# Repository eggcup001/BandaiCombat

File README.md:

# ATtiny85 Combat LED Game

ATtiny85 を使ってバンダイ「コンバット」風のLSIゲームを再現するための C プロジェクトです。

## Hardware

- MCU: ATtiny85, internal 8MHz, 3V
- LED matrix: 5 x 4
- 74HC595 x 2: LED anode bus and row/digit selection
- Buttons: 5-button ADC ladder
- Display: two common-cathode 7-segment digits
- Sound: 9042_16R electromagnetic passive buzzer

## Pin assignment

| Pin | Role |
|---|---|
| PB0 | 74HC595 SER |
| PB1 | 74HC595 SRCLK |
| PB2 | 74HC595 RCLK / LATCH |
| PB3 | ADC button ladder |
| PB4 | Buzzer driver |

## Display

U4 is the tens digit and U5 is the ones digit.

```text
U4 U5
 0  0   counter 00
    3   score 3
```

- Wait screen: score
- Game start: counter starts at `00`
- Normal play: zero-padded up-counter
- Enemy defeated: score for about 500 ms, then the next stage waits for FIRE
- Game over: the final score remains visible
- FIRE starts or restarts the game directly

## Game notes

- Mines are invisible.
- Mine proximity in the four orthogonally adjacent cells is indicated by sound only.
- Diagonal mines are not detected and do not produce the warning sound.
- The mine warning uses a low 1100 Hz pulse, distinct from the normal 2500 Hz tick.
- The death effect is a low descending tone from 1500 Hz to 500 Hz.
- Player is bright.
- Enemy uses one-eighth brightness and blinks on wait screens.
- Enemy dimming is scan-synchronized at about 83 Hz to avoid visible flicker.
- Mine placement always preserves a safe path to an orthogonally adjacent
  attack position next to the enemy.
- Stage randomization mixes PB3 ADC noise with the timing of FIRE input.
- Startup samples the PB3 ADC repeatedly before generating the first stage.
- The first stage shown during the wait screen is kept unchanged when FIRE
  starts play.
- Death restarts the same stage layout.
- Press FIRE to enter attack mode, then press a direction key to attack the
  adjacent cell in that direction.
- The direction key is consumed by the attack and does not move the player.
- A missed attack returns to movement mode without moving the player.
- A successful attack prepares the next round and waits for FIRE before play resumes.
- Press FIRE again while in attack mode to cancel it and return to movement
  mode.

## Build

```bash
make
```

## Flash

```bash
make flash
```

## Fuse example

```bash
make fuse
```

Fuse values:

- LFUSE: `0xE2`
- HFUSE: `0xDF`
- EFUSE: `0xFF`

These are intended for internal 8MHz, CKDIV8 disabled, reset enabled, BOD disabled.

## Important hardware tuning

`src/layer2/buttons.c` contains ADC thresholds.  
These must be adjusted using real measured ADC values.

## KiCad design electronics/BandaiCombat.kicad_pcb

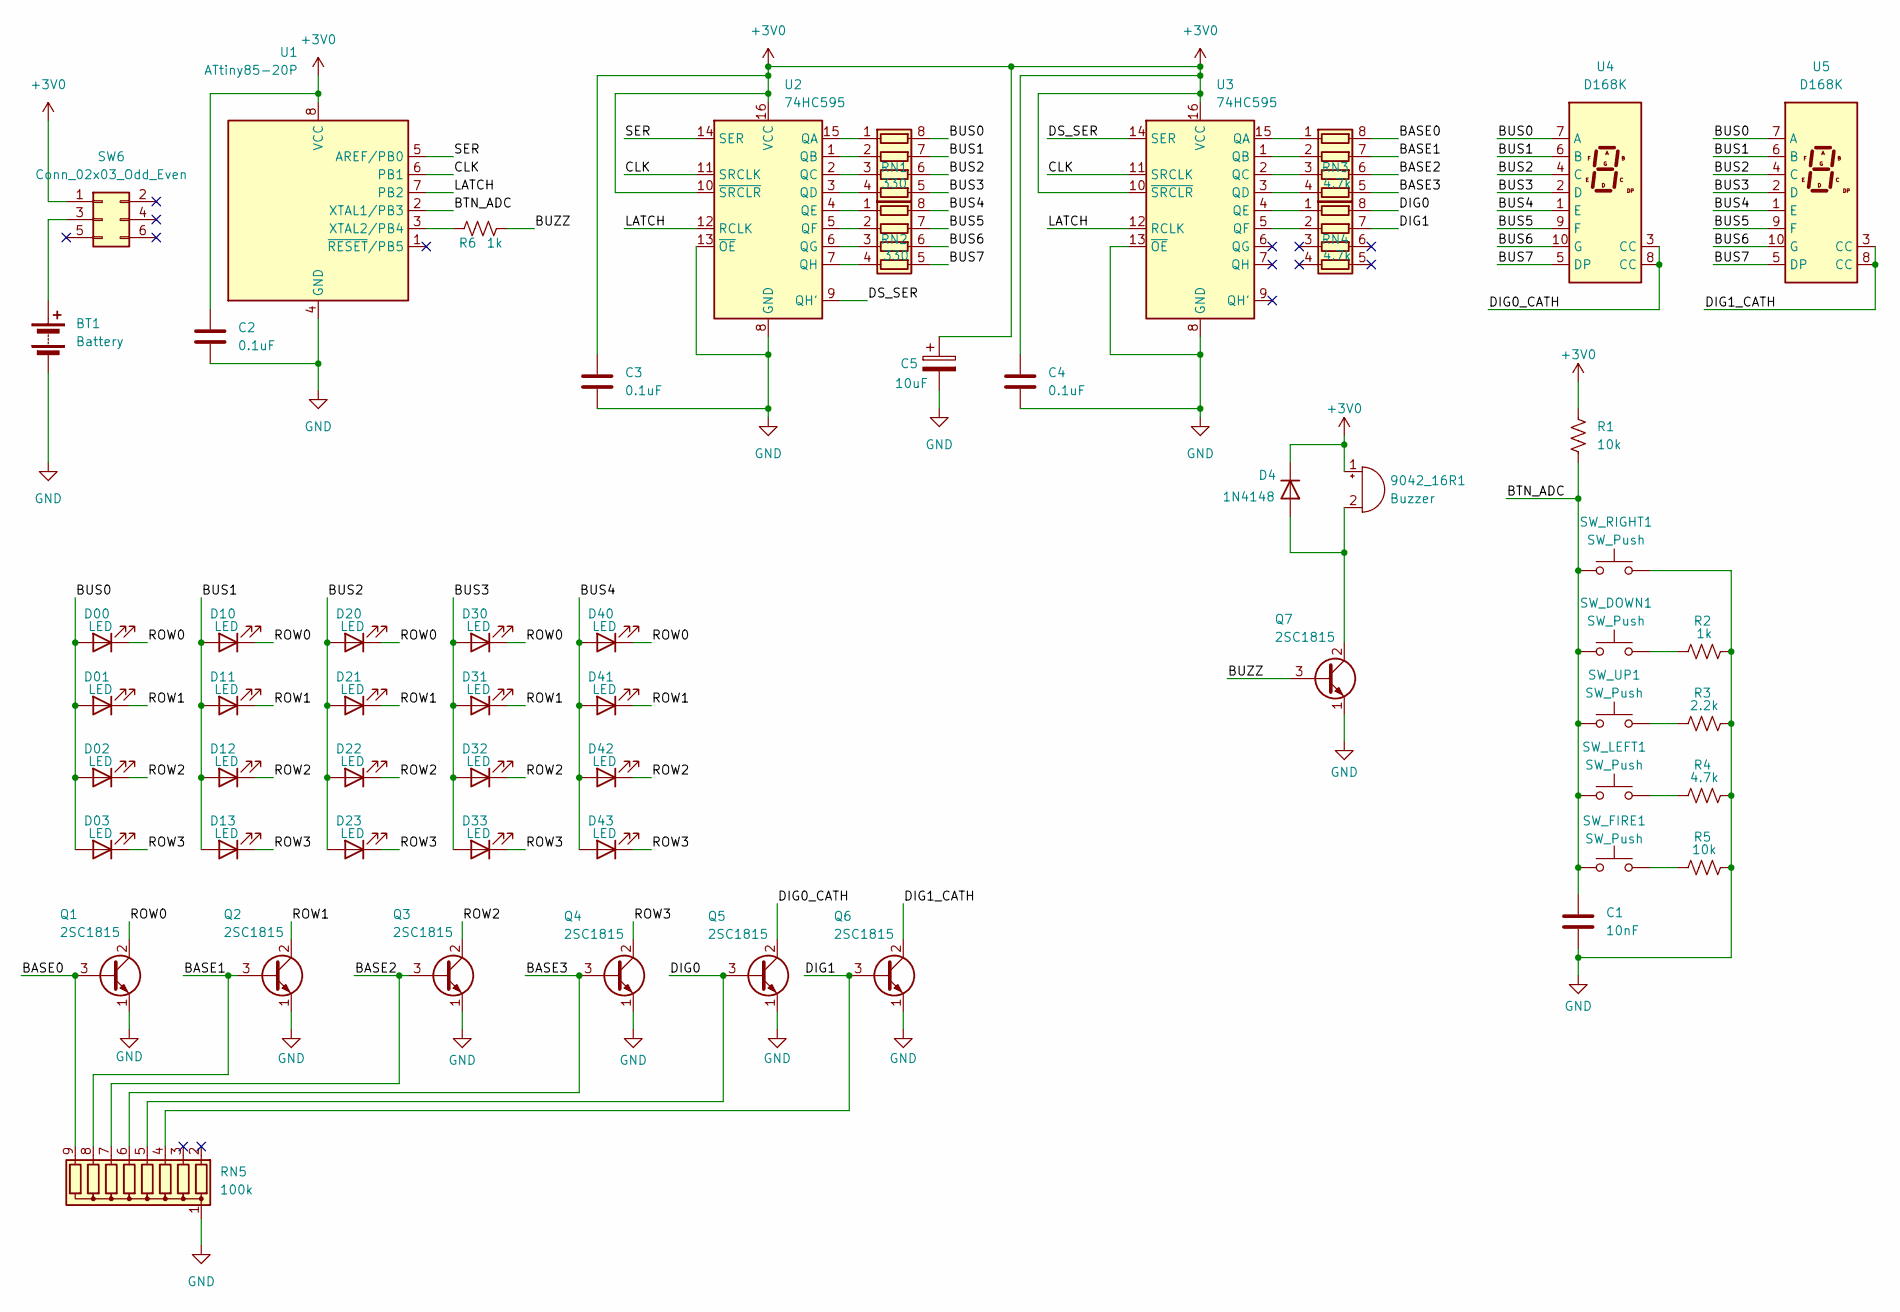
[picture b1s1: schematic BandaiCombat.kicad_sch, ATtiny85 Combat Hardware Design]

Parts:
9042_16R1: Buzzer; MagneticBuzzer_PUI_AT-0927-TT-6-R
BT1: Battery; PinHeader_1x02_P2.54mm_Vertical
C1: 10nF; C_Disc_D5.0mm_W2.5mm_P5.00mm
C2, C3, C4: 0.1uF; C_Disc_D5.0mm_W2.5mm_P5.00mm
C5: 10uF; CP_Radial_D5.0mm_P2.00mm
D00, D01, D02, D03, D10, D11, D12, D13, D20, D21, D22, D23, D30, D31, D32, D33, D40, D41, D42, D43: LED; LED_D5.0mm
D4: 1N4148; D_DO-35_SOD27_P7.62mm_Horizontal
Q1, Q2, Q3, Q4, Q5, Q6, Q7: 2SC1815; TO-92_Inline
R1, R5: 10k; R_Axial_DIN0207_L6.3mm_D2.5mm_P7.62mm_Horizontal
R2, R6: 1k; R_Axial_DIN0207_L6.3mm_D2.5mm_P7.62mm_Horizontal
R3: 2.2k; R_Axial_DIN0207_L6.3mm_D2.5mm_P7.62mm_Horizontal
R4: 4.7k; R_Axial_DIN0207_L6.3mm_D2.5mm_P7.62mm_Horizontal
RN1, RN2: 330; R_Array_Convex_4x0603
RN3, RN4: 4.7k; R_Array_Convex_4x0603
RN5: 100k; R_Array_SIP9
SW6: Conn_02x03_Odd_Even; PinHeader_2x03_P2.54mm_Vertical
SW_DOWN1: SW_Push; SW_PUSH_6mm
SW_FIRE1: SW_Push; SW_PUSH_6mm
SW_LEFT1: SW_Push; SW_PUSH_6mm
SW_RIGHT1: SW_Push; SW_PUSH_6mm
SW_UP1: SW_Push; SW_PUSH_6mm
U1: ATtiny85-20P; DIP-8_W7.62mm
U2, U3: 74HC595; DIP-16_W7.62mm
U4, U5: D168K; D1X8K

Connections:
+3V0: 9042_16R1.1 (+), C2.1, C3.1, C4.1, C5.1, D4.1 (K), R1.1, SW6.1, U1.8 (VCC), U2.10 (~SRCLR), U2.16 (VCC), U3.10 (~SRCLR), U3.16 (VCC)
/BASE0: Q1.3 (B), RN3.8 (R1.2), RN5.9 (R8)
/BASE1: Q2.3 (B), RN3.7 (R2.2), RN5.8 (R7)
/BASE2: Q3.3 (B), RN3.6 (R3.2), RN5.7 (R6)
/BASE3: Q4.3 (B), RN3.5 (R4.2), RN5.6 (R5)
/BTN_ADC: C1.1, R1.2, SW_DOWN1.1, SW_FIRE1.1, SW_LEFT1.1, SW_RIGHT1.1, SW_UP1.1, U1.2 (XTAL1/PB3)
/BUS0: D00.2 (A), D01.2 (A), D02.2 (A), D03.2 (A), RN1.8 (R1.2), U4.7 (A), U5.7 (A)
/BUS1: D10.2 (A), D11.2 (A), D12.2 (A), D13.2 (A), RN1.7 (R2.2), U4.6 (B), U5.6 (B)
/BUS2: D20.2 (A), D21.2 (A), D22.2 (A), D23.2 (A), RN1.6 (R3.2), U4.4 (C), U5.4 (C)
/BUS3: D30.2 (A), D31.2 (A), D32.2 (A), D33.2 (A), RN1.5 (R4.2), U4.2 (D), U5.2 (D)
/BUS4: D40.2 (A), D41.2 (A), D42.2 (A), D43.2 (A), RN2.8 (R1.2), U4.1 (E), U5.1 (E)
/BUS5: RN2.7 (R2.2), U4.9 (F), U5.9 (F)
/BUS6: RN2.6 (R3.2), U4.10 (G), U5.10 (G)
/BUS7: RN2.5 (R4.2), U4.5 (DP), U5.5 (DP)
/BUZZ: Q7.3 (B), R6.2
/CLK: U1.6 (PB1), U2.11 (SRCLK), U3.11 (SRCLK)
/DIG0: Q5.3 (B), RN4.8 (R1.2), RN5.5 (R4)
/DIG0_CATH: Q5.2 (C), U4.3 (CC), U4.8 (CC)
/DIG1: Q6.3 (B), RN4.7 (R2.2), RN5.4 (R3)
/DIG1_CATH: Q6.2 (C), U5.3 (CC), U5.8 (CC)
/DS_SER: U2.9 (QH'), U3.14 (SER)
/LATCH: U1.7 (PB2), U2.12 (RCLK), U3.12 (RCLK)
/ROW0: D00.1 (K), D10.1 (K), D20.1 (K), D30.1 (K), D40.1 (K), Q1.2 (C)
/ROW1: D01.1 (K), D11.1 (K), D21.1 (K), D31.1 (K), D41.1 (K), Q2.2 (C)
/ROW2: D02.1 (K), D12.1 (K), D22.1 (K), D32.1 (K), D42.1 (K), Q3.2 (C)
/ROW3: D03.1 (K), D13.1 (K), D23.1 (K), D33.1 (K), D43.1 (K), Q4.2 (C)
/SER: U1.5 (AREF/PB0), U2.14 (SER)
GND: BT1.2 (-), C1.2, C2.2, C3.2, C4.2, C5.2, Q1.1 (E), Q2.1 (E), Q3.1 (E), Q4.1 (E), Q5.1 (E), Q6.1 (E), Q7.1 (E), R2.2, R3.2, R4.2, R5.2, RN5.1 (common), SW_RIGHT1.2, U1.4 (GND), U2.8 (GND), U2.13 (~OE), U3.8 (GND), U3.13 (~OE)
unnamed: 9042_16R1.2 (-), D4.2 (A), Q7.2 (C)
unnamed: BT1.1 (+), SW6.3
unnamed: R2.1, SW_DOWN1.2
unnamed: R3.1, SW_UP1.2
unnamed: R4.1, SW_LEFT1.2
unnamed: R5.1, SW_FIRE1.2
unnamed: RN1.1 (R1.1), U2.15 (QA)
unnamed: RN1.2 (R2.1), U2.1 (QB)
unnamed: RN1.3 (R3.1), U2.2 (QC)
unnamed: RN1.4 (R4.1), U2.3 (QD)
unnamed: RN2.1 (R1.1), U2.4 (QE)
unnamed: RN2.2 (R2.1), U2.5 (QF)
unnamed: RN2.3 (R3.1), U2.6 (QG)
unnamed: RN2.4 (R4.1), U2.7 (QH)
unnamed: RN3.1 (R1.1), U3.15 (QA)
unnamed: RN3.2 (R2.1), U3.1 (QB)
unnamed: RN3.3 (R3.1), U3.2 (QC)
unnamed: RN3.4 (R4.1), U3.3 (QD)
unnamed: RN4.1 (R1.1), U3.4 (QE)
unnamed: RN4.2 (R2.1), U3.5 (QF)
unnamed: R6.1, U1.3 (XTAL2/PB4)

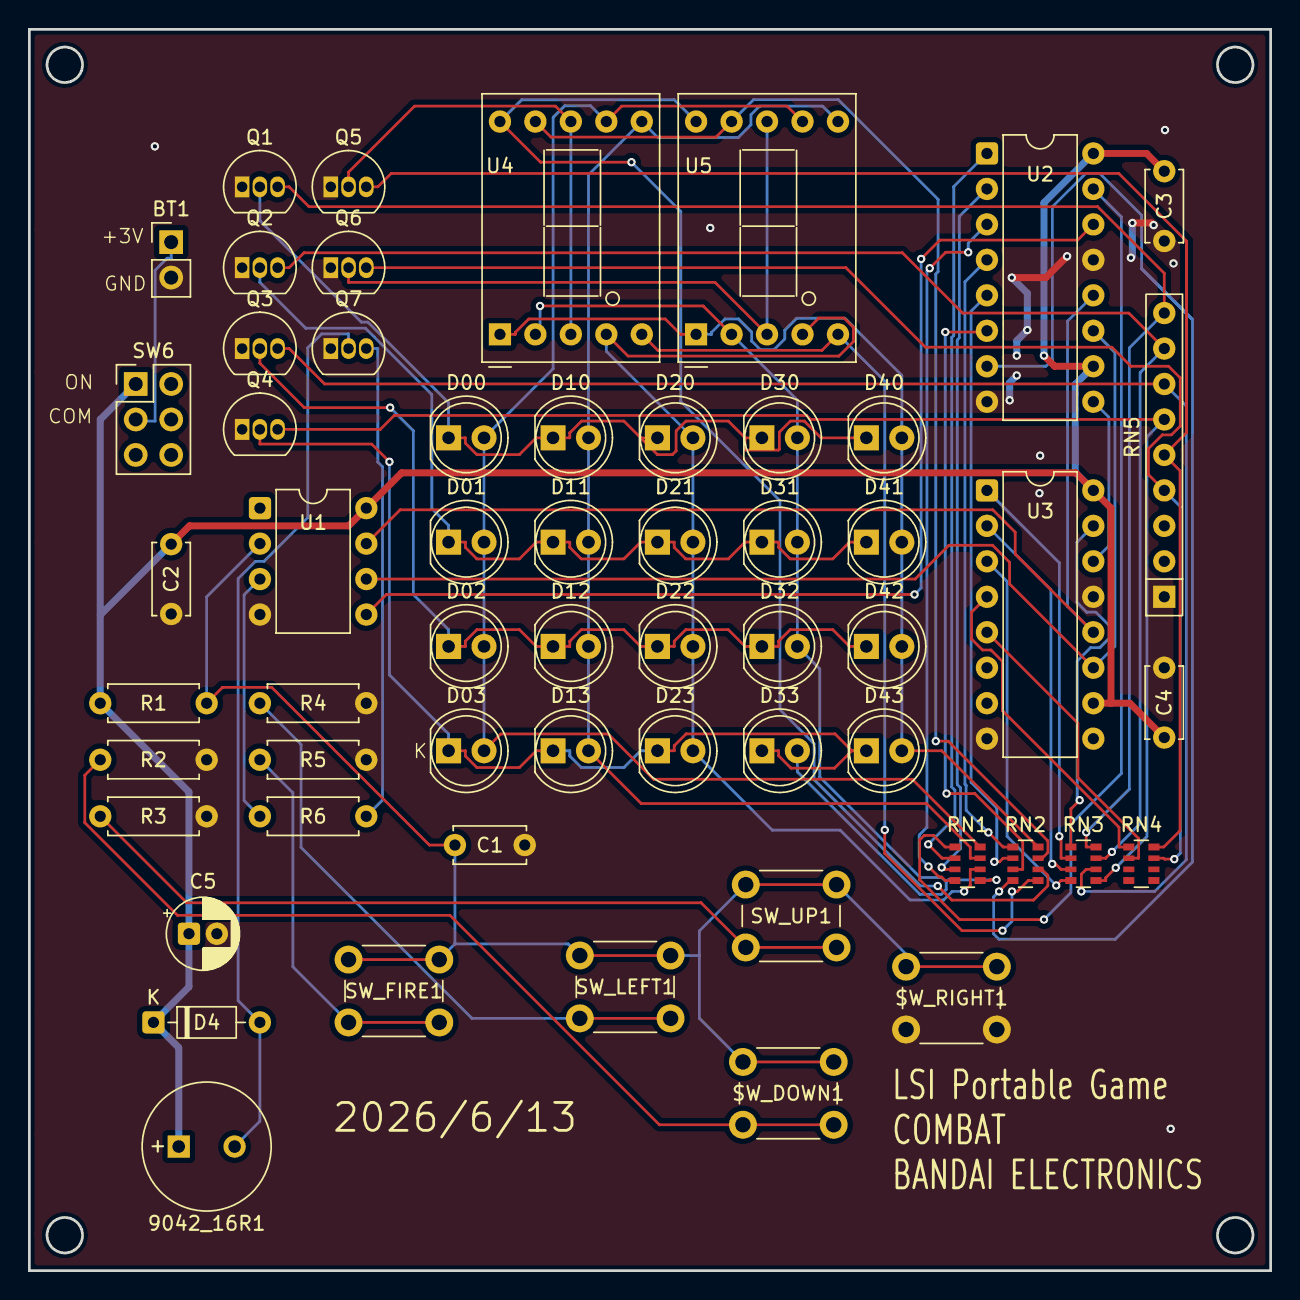
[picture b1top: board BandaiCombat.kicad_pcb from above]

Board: 2 copper layers, 88.9 x 88.9 mm, 57 parts (0 on the bottom side), 49 nets.

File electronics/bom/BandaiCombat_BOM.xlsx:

| Sourced | Placed | References | Value | Footprint | Quantity
1 |  |  | C2, C3, C4 | 0.1uF | C_Disc_D5.0mm_W2.5mm_P5.00mm | 3
2 |  |  | C1 | 10nF | C_Disc_D5.0mm_W2.5mm_P5.00mm | 1
3 |  |  | C5 | 10uF | CP_Radial_D5.0mm_P2.00mm | 1
4 |  |  | R1, R5 | 10k | R_Axial_DIN0207_L6.3mm_D2.5mm_P7.62mm_Horizontal | 2
5 |  |  | R2, R6 | 1k | R_Axial_DIN0207_L6.3mm_D2.5mm_P7.62mm_Horizontal | 2
6 |  |  | R3 | 2.2k | R_Axial_DIN0207_L6.3mm_D2.5mm_P7.62mm_Horizontal | 1
7 |  |  | R4 | 4.7k | R_Axial_DIN0207_L6.3mm_D2.5mm_P7.62mm_Horizontal | 1
8 |  |  | D00, D01, D02, D03, D10, D11, D12, D13, D20, D21, D22, D23, D30, D31, D32, D33,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 | LED | LED_D5.0mm | 20
9 |  |  | D4 | 1N4148 | D_DO-35_SOD27_P7.62mm_Horizontal | 1
10 |  |  | U2, U3 | 74HC595 | DIP-16_W7.62mm | 2
11 |  |  | U4, U5 | D168K | D1X8K | 2
12 |  |  | U1 | ATtiny85-20P | DIP-8_W7.62mm | 1
13 |  |  | SW6 | Conn_02x03_Odd_Even | PinHeader_2x03_P2.54mm_Vertical | 1
14 |  |  | Q1, Q2, Q3, Q4, Q5, Q6, Q7 | 2SC1815 | TO-92_Inline | 7
15 |  |  | SW_DOWN1, SW_FIRE1, SW_LEFT1, SW_RIGHT1, SW_UP1 | SW_Push | SW_PUSH_6mm | 5
16 |  |  | RN1, RN2 | 330 | R_Array_Convex_4x0603 | 2
17 |  |  | RN3, RN4 | 4.7k | R_Array_Convex_4x0603 | 2
18 |  |  | 9042_16R1 | Buzzer | MagneticBuzzer_PUI_AT-0927-TT-6-R | 1
19 |  |  | BT1 | Battery | PinHeader_1x02_P2.54mm_Vertical | 1
20 |  |  | RN5 | 100k | R_Array_SIP9 | 1

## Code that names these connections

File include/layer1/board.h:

#ifndef COMBAT_BOARD_H
#define COMBAT_BOARD_H

#ifndef F_CPU
#define F_CPU 8000000UL
#endif

#include "util/config.h"

#include <avr/io.h>

/*
 * Hardware specification for the ATtiny85 Combat project.
 *
 *   PB0 = 74HC595 serial data
 *   PB1 = 74HC595 shift clock
 *   PB2 = 74HC595 latch clock
 *   PB3 = button ADC ladder
 *   PB4 = passive buzzer driver
 */

#define PIN_SHIFT_SER     PB0
#define PIN_SHIFT_CLOCK   PB1
#define PIN_SHIFT_LATCH   PB2
#define PIN_ADC           PB3
#define PIN_BUZZER        PB4

/* U3 row/digit select output bit layout. */
#define SELECT_ROW0       0
#define SELECT_ROW1       1
#define SELECT_ROW2       2
#define SELECT_ROW3       3
#define SELECT_DIGIT0     4
#define SELECT_DIGIT1     5

#endif

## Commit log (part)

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2026-06-23 Add PCB fabrication files
2026-06-23 Add Bandai Combat schematic PDF
2026-06-24 Update from local workspace
2026-06-24 Remove .mp4 files and add to .gitignore
